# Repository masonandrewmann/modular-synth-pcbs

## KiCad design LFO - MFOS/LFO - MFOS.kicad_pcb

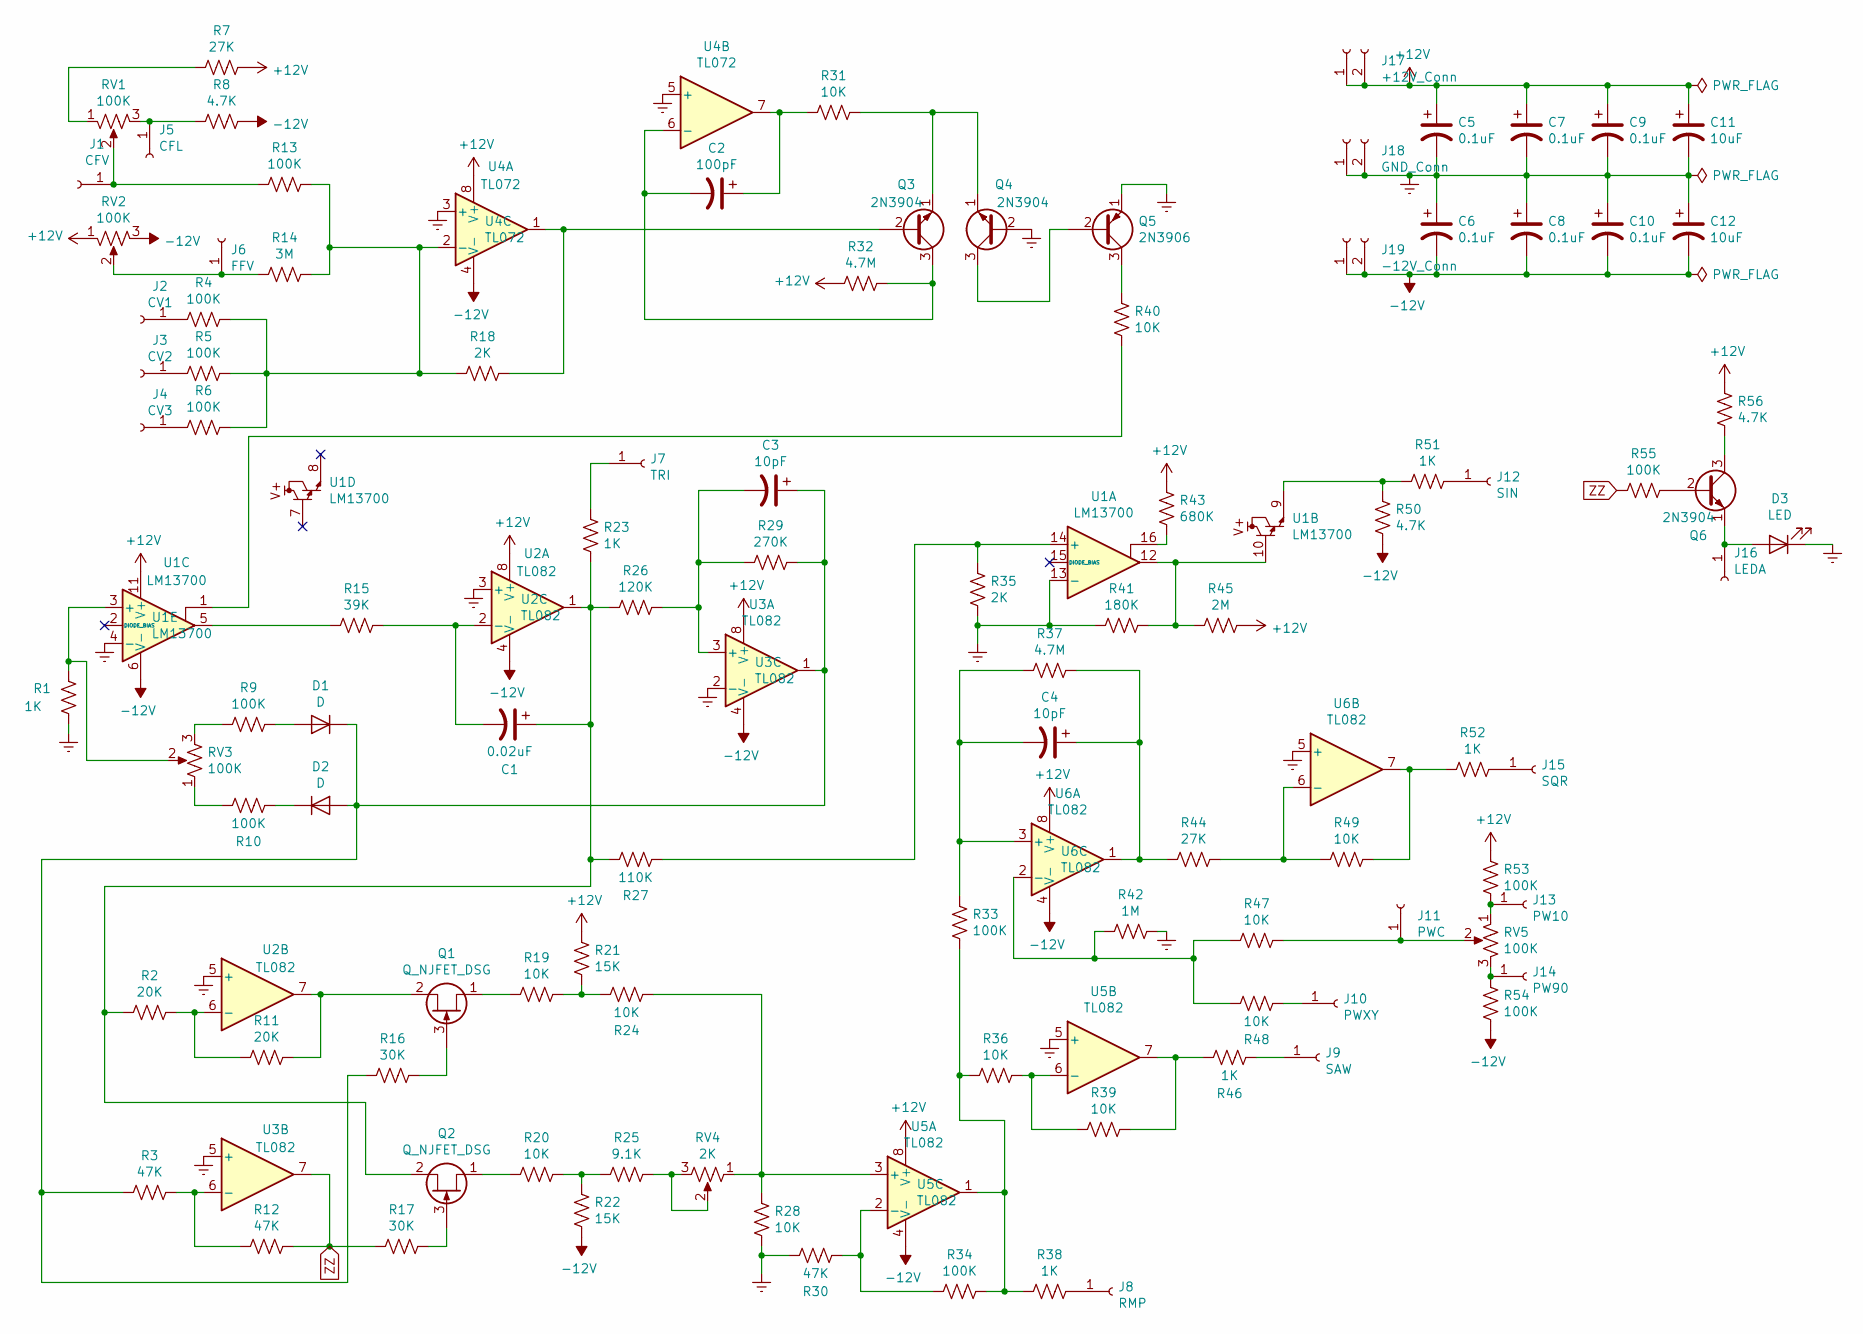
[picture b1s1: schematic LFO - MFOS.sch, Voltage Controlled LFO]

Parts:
C1: 0.02uF; C_Rect_L7.0mm_W2.5mm_P5.00mm
C2: 100pF; C_Rect_L7.0mm_W2.5mm_P5.00mm
C3, C4: 10pF; C_Rect_L7.0mm_W2.5mm_P5.00mm
C5, C6, C7, C8, C9, C10: 0.1uF; C_Rect_L7.0mm_W2.5mm_P5.00mm
C11, C12: 10uF; CP_Radial_D4.0mm_P2.00mm
D1, D2: D; D_T-1_P5.08mm_Horizontal
D3: LED
J1: CFV; SolderWirePad_1x01_Drill1mm
J2: CV1; SolderWirePad_1x01_Drill1mm
J3: CV2; SolderWirePad_1x01_Drill1mm
J4: CV3; SolderWirePad_1x01_Drill1mm
J5: CFL; SolderWirePad_1x01_Drill1mm
J6: FFV; SolderWirePad_1x01_Drill1mm
J7: TRI; SolderWirePad_1x01_Drill1mm
J8: RMP; SolderWirePad_1x01_Drill1mm
J9: SAW; SolderWirePad_1x01_Drill1mm
J10: PWXY; SolderWirePad_1x01_Drill1mm
J11: PWC; SolderWirePad_1x01_Drill1mm
J12: SIN; SolderWirePad_1x01_Drill1mm
J13: PW10; SolderWirePad_1x01_Drill1mm
J14: PW90; SolderWirePad_1x01_Drill1mm
J15: SQR; SolderWirePad_1x01_Drill1mm
J16: LEDA; SolderWirePad_1x01_Drill1mm
J17: +12V_Conn; SolderWirePad_1x02_P3.81mm_Drill1mm
J18: GND_Conn; SolderWirePad_1x02_P3.81mm_Drill1mm
J19: -12V_Conn; SolderWirePad_1x02_P3.81mm_Drill1mm
Q1, Q2: Q_NJFET_DSG; TO-92_Inline_Wide
Q3, Q4, Q6: 2N3904; TO-92_Inline_Wide
Q5: 2N3906; TO-92_Inline_Wide
R1, R23, R38, R46, R51, R52: 1K; R_Axial_DIN0207_L6.3mm_D2.5mm_P7.62mm_Horizontal
R2, R11: 20K; R_Axial_DIN0207_L6.3mm_D2.5mm_P7.62mm_Horizontal
R3, R12, R30: 47K; R_Axial_DIN0207_L6.3mm_D2.5mm_P7.62mm_Horizontal
R4, R5, R6, R9, R10, R13, R33, R34, R53, R54, R55: 100K; R_Axial_DIN0207_L6.3mm_D2.5mm_P7.62mm_Horizontal
R7, R44: 27K; R_Axial_DIN0207_L6.3mm_D2.5mm_P7.62mm_Horizontal
R8, R50, R56: 4.7K; R_Axial_DIN0207_L6.3mm_D2.5mm_P7.62mm_Horizontal
R14: 3M; R_Axial_DIN0207_L6.3mm_D2.5mm_P7.62mm_Horizontal
R15: 39K; R_Axial_DIN0207_L6.3mm_D2.5mm_P7.62mm_Horizontal
R16, R17: 30K; R_Axial_DIN0207_L6.3mm_D2.5mm_P7.62mm_Horizontal
R18, R35: 2K; R_Axial_DIN0207_L6.3mm_D2.5mm_P7.62mm_Horizontal
R19, R20, R24, R28, R31, R36, R39, R40, R47, R48, R49: 10K; R_Axial_DIN0207_L6.3mm_D2.5mm_P7.62mm_Horizontal
R21, R22: 15K; R_Axial_DIN0207_L6.3mm_D2.5mm_P7.62mm_Horizontal
R25: 9.1K; R_Axial_DIN0207_L6.3mm_D2.5mm_P7.62mm_Horizontal
R26: 120K; R_Axial_DIN0207_L6.3mm_D2.5mm_P7.62mm_Horizontal
R27: 110K; R_Axial_DIN0207_L6.3mm_D2.5mm_P7.62mm_Horizontal
R29: 270K; R_Axial_DIN0207_L6.3mm_D2.5mm_P7.62mm_Horizontal
R32, R37: 4.7M; R_Axial_DIN0207_L6.3mm_D2.5mm_P7.62mm_Horizontal
R41: 180K; R_Axial_DIN0207_L6.3mm_D2.5mm_P7.62mm_Horizontal
R42: 1M; R_Axial_DIN0207_L6.3mm_D2.5mm_P7.62mm_Horizontal
R43: 680K; R_Axial_DIN0207_L6.3mm_D2.5mm_P7.62mm_Horizontal
R45: 2M; R_Axial_DIN0207_L6.3mm_D2.5mm_P7.62mm_Horizontal
RV1, RV2, RV5: 100K
RV3: 100K; Potentiometer_Runtron_RM-065_Vertical
RV4: 2K; Potentiometer_Runtron_RM-065_Vertical
U1: LM13700; DIP-16_W7.62mm_Socket
U2, U3, U5, U6: TL082; DIP-8_W7.62mm_Socket
U4: TL072; DIP-8_W7.62mm_Socket

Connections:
+12V: C5.1, C7.1, C9.1, C11.1, J17.1, J17.2, R7.1, R21.2, R32.2, R43.2, R45.1, R53.1, R56.2, RV2.1, U1.11 (V+), U2.8 (V+), U3.8 (V+), U4.8 (V+), U5.8 (V+), U6.8 (V+)
-12V: C6.2, C8.2, C10.2, C12.2, J19.1, J19.2, R8.1, R22.1, R50.1, R54.2, RV2.3, U1.6 (V-), U2.4 (V-), U3.4 (V-), U4.4 (V-), U5.4 (V-), U6.4 (V-)
Earth: C5.2, C6.1, C7.2, C8.1, C9.2, C10.1, C11.2, C12.1, D3.1 (K), J18.1, J18.2, Q4.2 (B), Q5.1 (E), R1.2, R28.1, R30.2, R35.1, R41.2, R42.1, U1.4 (-), U1.13 (-), U2.3 (+), U2.5 (+), U3.2 (-), U3.5 (+), U4.3 (+), U4.5 (+), U5.5 (+), U6.5 (+)
unnamed: C1.1, Q2.2 (S), R2.2, R23.1, R26.2, R27.2, U2.1
unnamed: C1.2, R15.1, U2.2 (-)
unnamed: C2.1, R31.2, U4.7
unnamed: C2.2, Q3.3 (C), R32.1, U4.6 (-)
unnamed: C3.1, D1.1 (K), D2.2 (A), R3.2, R16.2, R29.1, U3.1
unnamed: C3.2, R26.1, R29.2, U3.3 (+)
unnamed: C4.1, R37.1, R44.1, U6.1
unnamed: C4.2, R33.2, R37.2, U6.3 (+)
unnamed: D1.2 (A), R9.1
unnamed: D2.1 (K), R10.1
unnamed: D3.2 (A), J16.1, Q6.1 (E)
unnamed: J1.1, R13.2, RV1.2
unnamed: J2.1, R4.2
unnamed: J3.1, R5.2
unnamed: J4.1, R6.2
unnamed: J5.1, R8.2, RV1.3
unnamed: J6.1, R14.2, RV2.2
unnamed: J7.1, R23.2
unnamed: J8.1, R38.1
unnamed: J9.1, R46.1
unnamed: J10.1, R48.2
unnamed: J11.1, R47.2, RV5.2
unnamed: J12.1, R51.1
unnamed: J13.1, R53.2, RV5.1
unnamed: J14.1, R54.1, RV5.3
unnamed: J15.1, R52.2
unnamed: Q1.1 (D), R19.2
unnamed: Q1.2 (S), R11.1, U2.7
unnamed: Q1.3 (G), R16.1
unnamed: Q2.1 (D), R20.2
unnamed: Q2.3 (G), R17.1
unnamed: Q3.1 (E), Q4.1 (E), R31.1
unnamed: Q3.2 (B), R18.2, U4.1
unnamed: Q4.3 (C), Q5.2 (B)
unnamed: Q5.3 (C), R40.2
unnamed: Q6.2 (B), R55.1
unnamed: Q6.3 (C), R56.1
unnamed: R1.1, RV3.2, U1.3 (+)
unnamed: R7.2, RV1.1
unnamed: R9.2, RV3.3
unnamed: R10.2, RV3.1
unnamed: R2.1, R11.2, U2.6 (-)
unnamed: R3.1, R12.2, U3.6 (-)
unnamed: R4.1, R5.1, R6.1, R13.1, R14.1, R18.1, U4.2 (-)
unnamed: R15.2, U1.5
unnamed: R19.1, R21.1, R24.2
unnamed: R20.1, R22.2, R25.2
unnamed: R24.1, R28.2, RV4.1, U5.3 (+)
unnamed: R25.1, RV4.2, RV4.3
unnamed: R27.1, R35.2, U1.14 (+)
unnamed: R30.1, R34.2, U5.2 (-)
unnamed: R33.1, R34.1, R36.2, R38.2, U5.1
unnamed: R36.1, R39.2, U5.6 (-)
unnamed: R39.1, R46.2, U5.7
unnamed: R40.1, U1.1
unnamed: R41.1, R45.2, U1.10, U1.12
unnamed: R42.2, R47.1, R48.1, U6.2 (-)
unnamed: R43.1, U1.16
unnamed: R44.2, R49.1, U6.6 (-)
unnamed: R49.2, R52.1, U6.7
unnamed: R50.2, R51.2, U1.9
ZZ: R12.1, R17.2, R55.2, U3.7

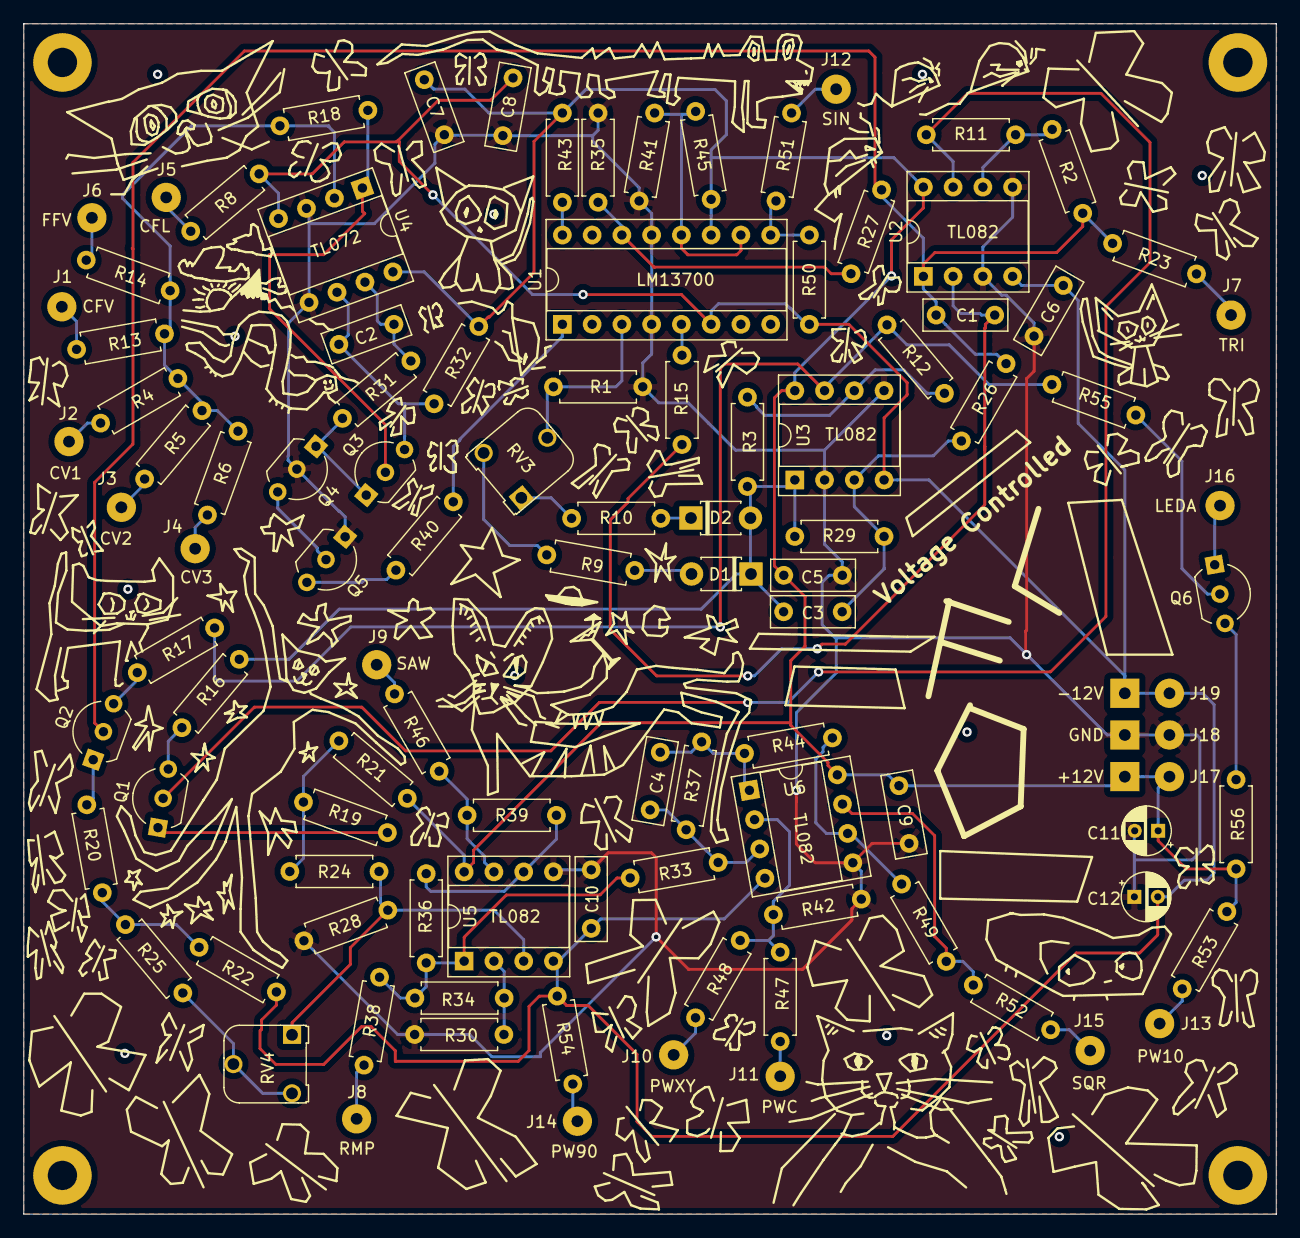
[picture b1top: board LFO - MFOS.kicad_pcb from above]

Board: 2 copper layers, 106.9 x 101.6 mm, 102 parts (0 on the bottom side), 64 nets.

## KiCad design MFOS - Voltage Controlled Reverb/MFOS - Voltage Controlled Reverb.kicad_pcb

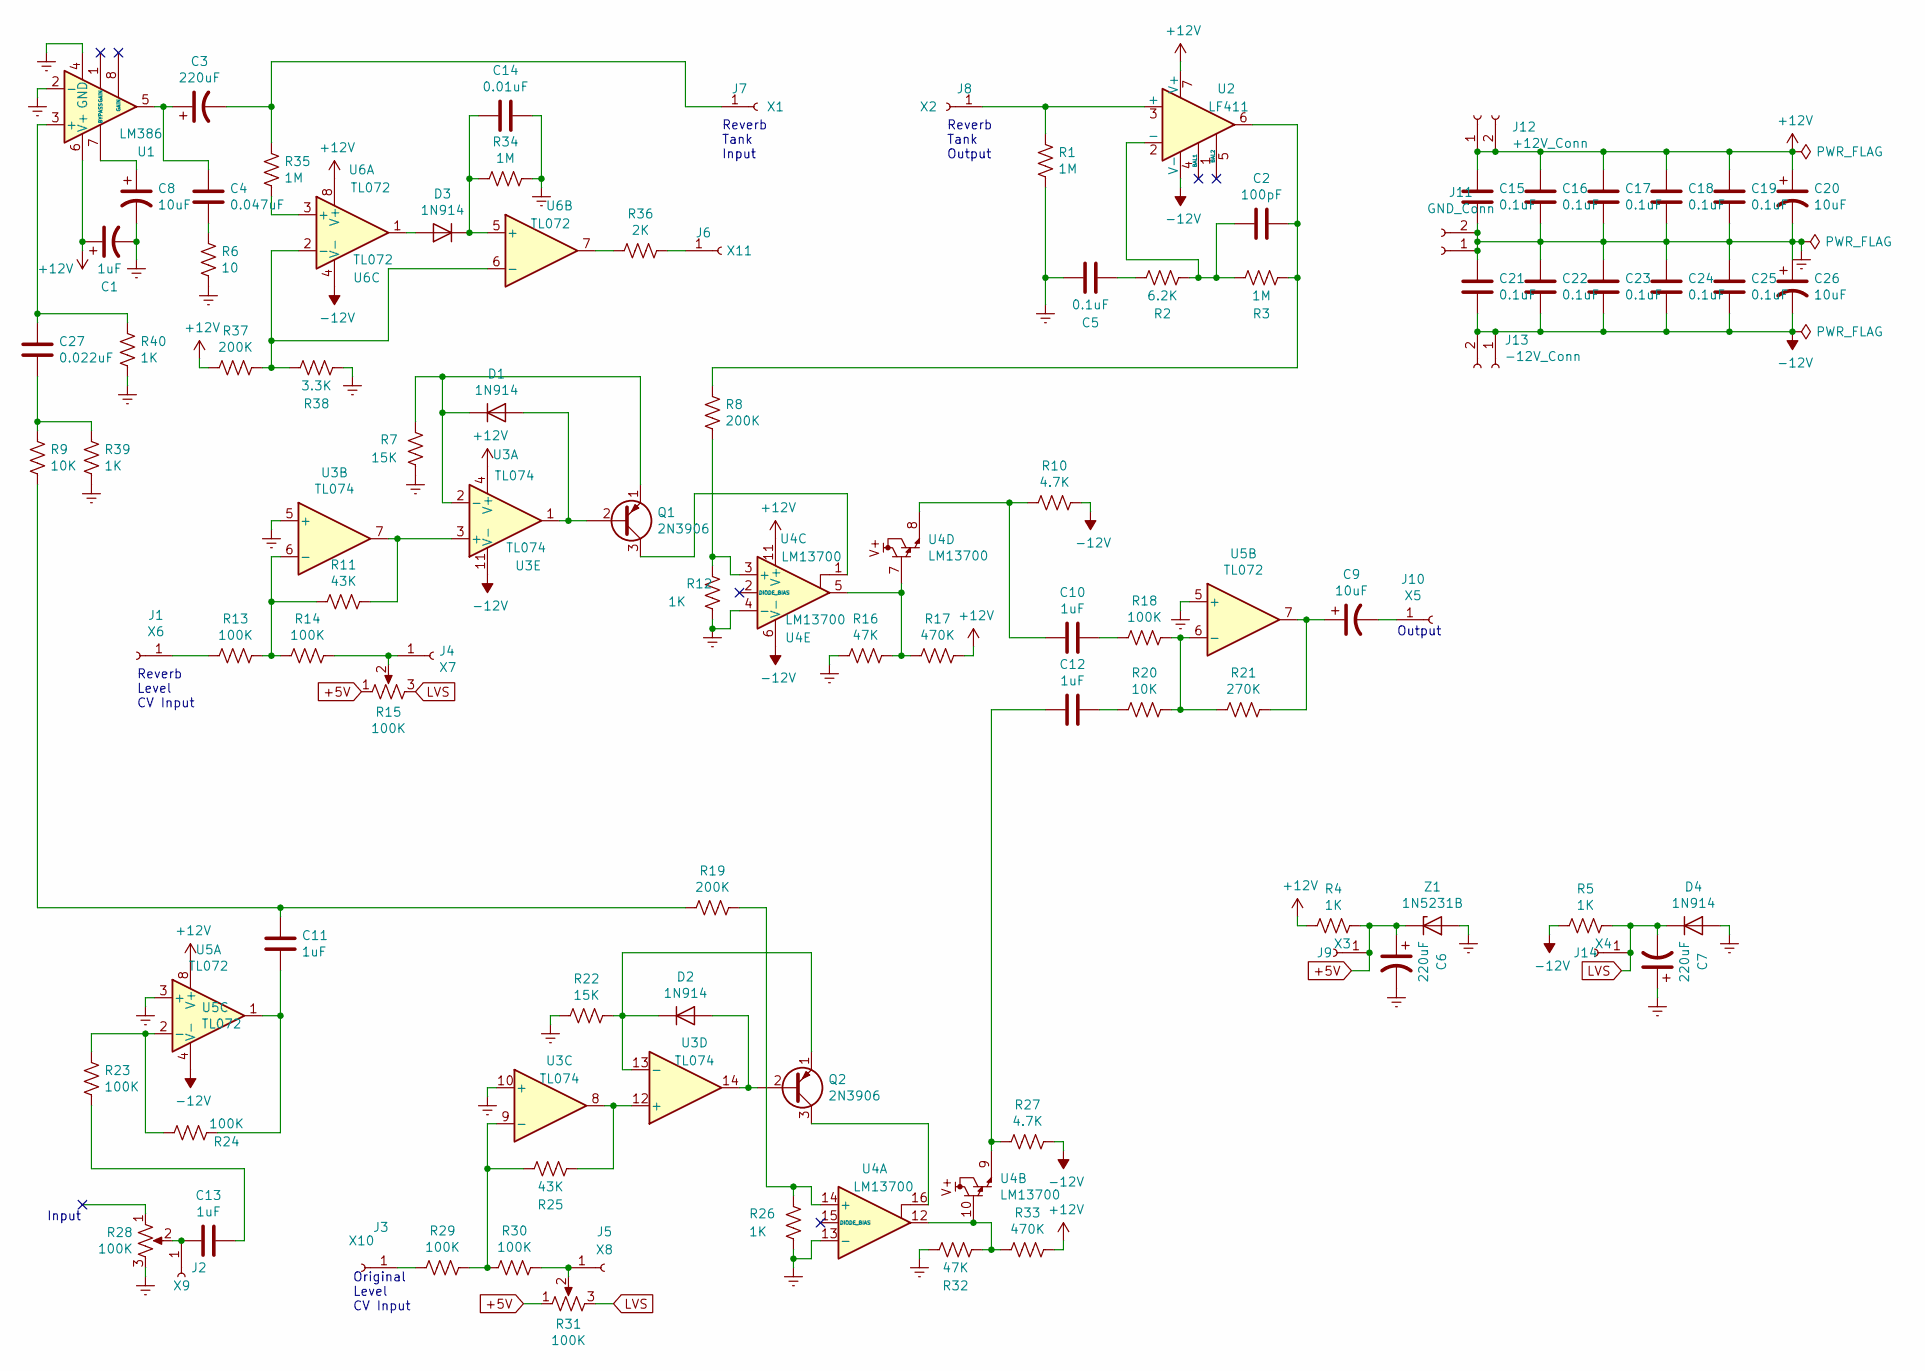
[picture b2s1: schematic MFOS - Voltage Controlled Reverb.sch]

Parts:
C1, C10, C11, C12, C13: 1uF; C_Rect_L7.0mm_W2.5mm_P5.00mm
C2: 100pF; C_Rect_L7.0mm_W2.5mm_P5.00mm
C3: 220uF; C_Rect_L7.0mm_W2.5mm_P5.00mm
C4: 0.047uF; C_Rect_L7.0mm_W2.5mm_P5.00mm
C5, C15, C16, C17, C18, C19, C21, C22, C23, C24, C25: 0.1uF; C_Rect_L7.0mm_W2.5mm_P5.00mm
C6, C7: 220uF; CP_Radial_D8.0mm_P3.50mm
C8, C9, C20, C26: 10uF; CP_Radial_D8.0mm_P3.50mm
C14: 0.01uF; C_Rect_L7.0mm_W2.5mm_P5.00mm
C27: 0.022uF; C_Rect_L7.0mm_W2.5mm_P5.00mm
D1, D2, D3, D4: 1N914; D_T-1_P5.08mm_Horizontal
J1: X6; SolderWirePad_1x01_Drill1mm
J2: X9; SolderWirePad_1x01_Drill1mm
J3: X10; SolderWirePad_1x01_Drill1mm
J4: X7; SolderWirePad_1x01_Drill1mm
J5: X8; SolderWirePad_1x01_Drill1mm
J6: X11; SolderWirePad_1x01_Drill1mm
J7: X1; SolderWirePad_1x01_Drill1mm
J8: X2; SolderWirePad_1x01_Drill1mm
J9: X3; SolderWirePad_1x01_Drill1mm
J10: X5; SolderWirePad_1x01_Drill1mm
J11: GND_Conn; SolderWirePad_1x02_P3.81mm_Drill1mm
J12: +12V_Conn; SolderWirePad_1x02_P3.81mm_Drill1mm
J13: -12V_Conn; SolderWirePad_1x02_P3.81mm_Drill1mm
J14: X4; SolderWirePad_1x01_Drill1mm
Q1, Q2: 2N3906; TO-92_Inline_Wide
R1, R3, R34, R35: 1M; R_Axial_DIN0207_L6.3mm_D2.5mm_P7.62mm_Horizontal
R2: 6.2K; R_Axial_DIN0207_L6.3mm_D2.5mm_P7.62mm_Horizontal
R4, R5, R12, R26, R39, R40: 1K; R_Axial_DIN0207_L6.3mm_D2.5mm_P7.62mm_Horizontal
R6: 10; R_Axial_DIN0207_L6.3mm_D2.5mm_P7.62mm_Horizontal
R7, R22: 15K; R_Axial_DIN0207_L6.3mm_D2.5mm_P7.62mm_Horizontal
R8, R19, R37: 200K; R_Axial_DIN0207_L6.3mm_D2.5mm_P7.62mm_Horizontal
R9, R20: 10K; R_Axial_DIN0207_L6.3mm_D2.5mm_P7.62mm_Horizontal
R10, R27: 4.7K; R_Axial_DIN0207_L6.3mm_D2.5mm_P7.62mm_Horizontal
R11, R25: 43K; R_Axial_DIN0207_L6.3mm_D2.5mm_P7.62mm_Horizontal
R13, R14, R18, R23, R24, R29, R30: 100K; R_Axial_DIN0207_L6.3mm_D2.5mm_P7.62mm_Horizontal
R15, R28, R31: 100K; Valve_Mini_G
R16, R32: 47K; R_Axial_DIN0207_L6.3mm_D2.5mm_P7.62mm_Horizontal
R17, R33: 470K; R_Axial_DIN0207_L6.3mm_D2.5mm_P7.62mm_Horizontal
R21: 270K; R_Axial_DIN0207_L6.3mm_D2.5mm_P7.62mm_Horizontal
R36: 2K; R_Axial_DIN0207_L6.3mm_D2.5mm_P7.62mm_Horizontal
R38: 3.3K; R_Axial_DIN0207_L6.3mm_D2.5mm_P7.62mm_Horizontal
U1: LM386; DIP-8_W7.62mm_Socket
U2: LF411; DIP-8_W7.62mm_Socket
U3: TL074; DIP-14_W7.62mm_Socket
U4: LM13700; DIP-16_W7.62mm_Socket
U5, U6: TL072; DIP-8_W7.62mm_Socket
Z1: 1N5231B; D_T-1_P5.08mm_Horizontal

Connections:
+5V: C6.1, J9.1, R4.2, R15.1, R31.1, Z1.1 (K)
+12V: C1.1, C15.1, C16.1, C17.1, C18.1, C19.1, C20.1, J12.1, J12.2, R4.1, R17.2, R33.2, R37.2, U1.6 (V+), U2.7 (V+), U3.4 (V+), U4.11 (V+), U5.8 (V+), U6.8 (V+)
-12V: C21.2, C22.2, C23.2, C24.2, C25.2, C26.2, J13.1, J13.2, R5.1, R10.2, R27.2, U2.4 (V-), U3.11 (V-), U4.6 (V-), U5.4 (V-), U6.4 (V-)
Earth: C1.2, C5.2, C6.2, C7.1, C8.2, C14.1, C15.2, C16.2, C17.2, C18.2, C19.2, C20.2, C21.1, C22.1, C23.1, C24.1, C25.1, C26.1, D4.2 (A), J11.1, J11.2, R1.1, R6.2, R7.1, R12.1, R16.1, R22.2, R26.1, R28.3, R32.1, R34.1, R38.1, R39.2, R40.2, U1.2 (-), U1.4 (GND), U3.5 (+), U3.10 (+), U4.4 (-), U4.13 (-), U5.3 (+), U5.5 (+), Z1.2 (A)
LVS: C7.2, D4.1 (K), J14.1, R5.2, R15.3, R31.3
unnamed: C2.1, R3.2, R8.1, U2.6
unnamed: C2.2, R2.2, R3.1, U2.2 (-)
unnamed: C3.1, C4.1, U1.5
unnamed: C3.2, J7.1, R35.2
unnamed: C4.2, R6.1
unnamed: C5.1, R2.1
unnamed: C8.1, U1.7 (BYPASS)
unnamed: C9.1, R21.2, U5.7
unnamed: C9.2, J10.1
unnamed: C10.1, R18.1
unnamed: C10.2, R10.1, U4.8
unnamed: C11.1, R24.2, U5.1
unnamed: C11.2, R9.2, R19.2
unnamed: C12.1, R20.1
unnamed: C12.2, R27.1, U4.9
unnamed: C13.1, R23.1
unnamed: C13.2, J2.1, R28.2
unnamed: C14.2, D3.1 (K), R34.2, U6.5 (+)
unnamed: C27.1, R40.1, U1.3 (+)
unnamed: C27.2, R9.1, R39.1
unnamed: D1.1 (K), Q1.1 (E), R7.2, U3.2 (-)
unnamed: D1.2 (A), Q1.2 (B), U3.1
unnamed: D2.1 (K), Q2.1 (E), R22.1, U3.13 (-)
unnamed: D2.2 (A), Q2.2 (B), U3.14
unnamed: D3.2 (A), U6.1
unnamed: J1.1, R13.2
unnamed: J3.1, R29.2
unnamed: J4.1, R14.1, R15.2
unnamed: J5.1, R30.1, R31.2
unnamed: J6.1, R36.1
unnamed: J8.1, R1.2, U2.3 (+)
unnamed: Q1.3 (C), U4.1
unnamed: Q2.3 (C), U4.16
unnamed: R11.1, U3.3 (+), U3.7
unnamed: R11.2, R13.1, R14.2, U3.6 (-)
unnamed: R8.2, R12.2, U4.3 (+)
unnamed: R16.2, R17.1, U4.5, U4.7
unnamed: R18.2, R20.2, R21.1, U5.6 (-)
unnamed: R19.1, R26.2, U4.14 (+)
unnamed: R23.2, R24.1, U5.2 (-)
unnamed: R25.1, U3.8, U3.12 (+)
unnamed: R25.2, R29.1, R30.2, U3.9 (-)
unnamed: R32.2, R33.1, U4.10, U4.12
unnamed: R35.1, U6.3 (+)
unnamed: R36.2, U6.7
unnamed: R37.1, R38.2, U6.2 (-), U6.6 (-)

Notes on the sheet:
Output
Input
Original Level CV Input
Reverb Level CV Input
Reverb Tank Output
Reverb Tank Input

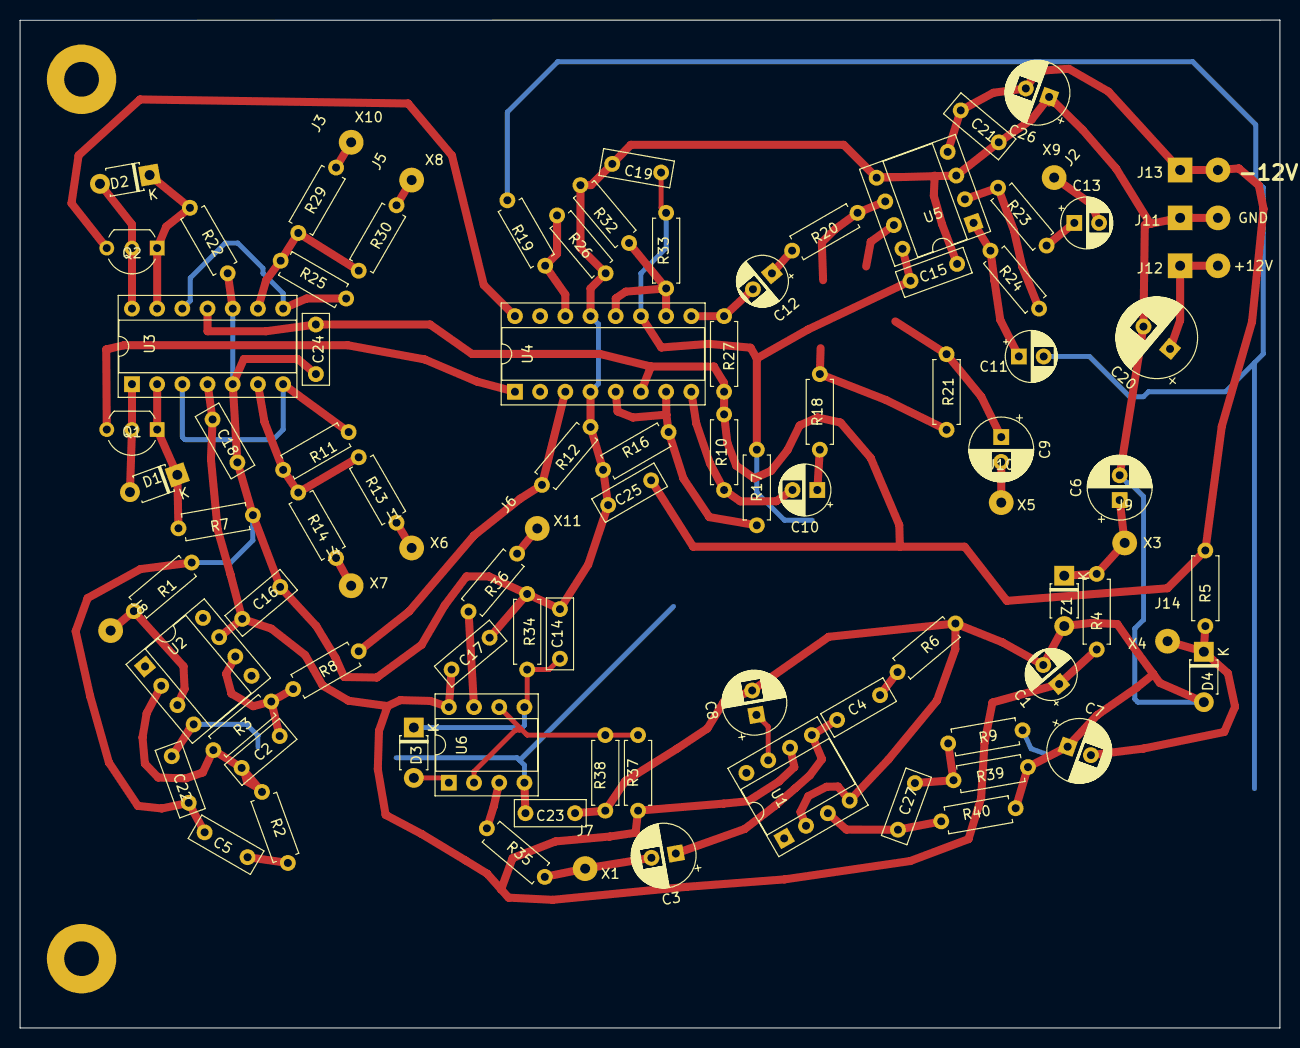
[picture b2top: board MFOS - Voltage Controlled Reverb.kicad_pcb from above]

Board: 2 copper layers, 127.0 x 101.6 mm, 91 parts (0 on the bottom side), 51 nets.

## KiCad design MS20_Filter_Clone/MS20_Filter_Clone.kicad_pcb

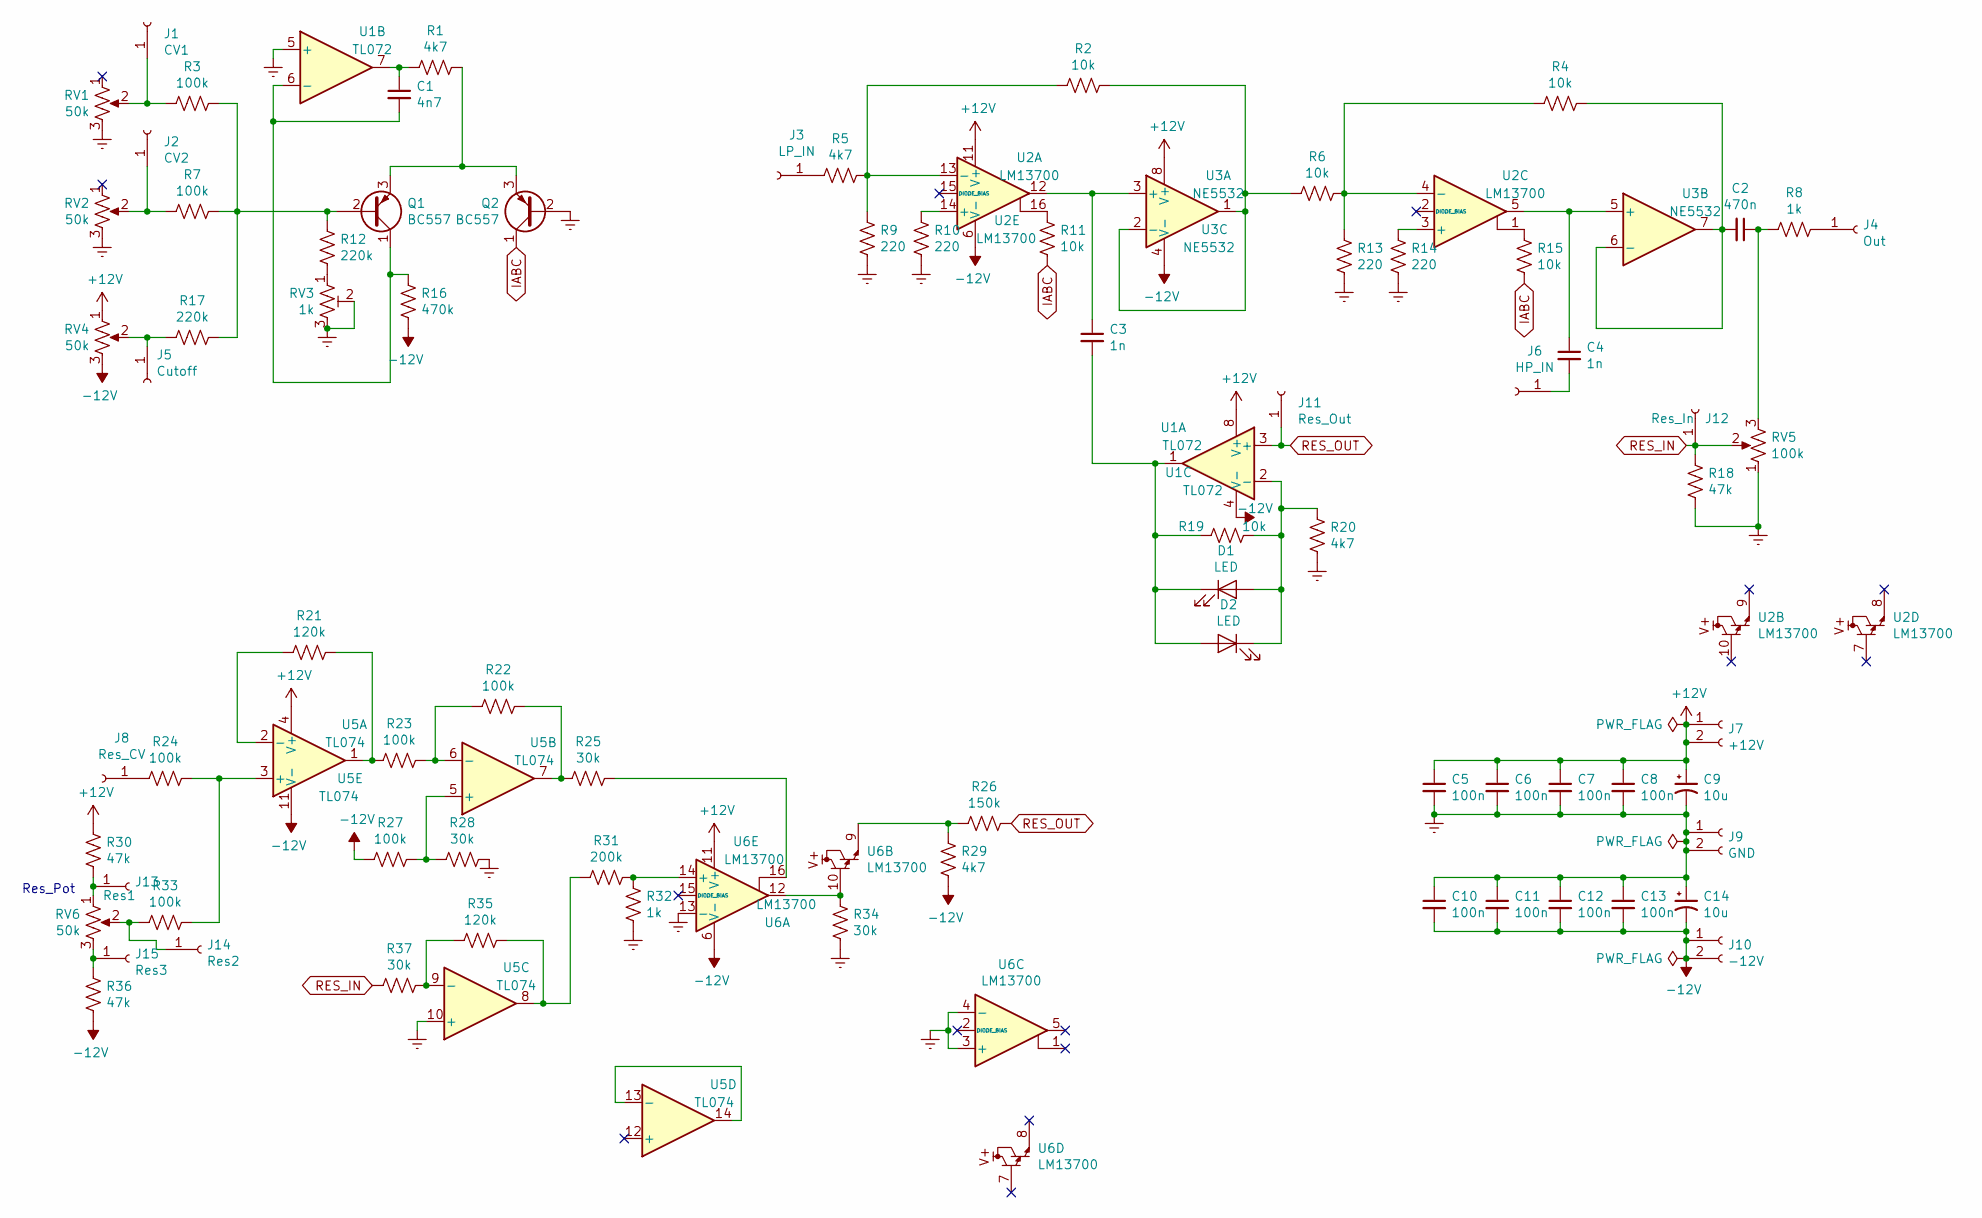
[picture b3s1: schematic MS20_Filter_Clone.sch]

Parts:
C1: 4n7; C_Rect_L7.0mm_W2.5mm_P5.00mm
C2: 470n; C_Rect_L7.0mm_W2.5mm_P5.00mm
C3, C4: 1n; C_Rect_L7.0mm_W2.5mm_P5.00mm
C5, C6, C7, C8, C10, C11, C12, C13: 100n; C_Rect_L7.0mm_W2.5mm_P5.00mm
C9, C14: 10u; CP_Radial_D5.0mm_P2.0mm_Bigger_Holes
D1, D2: LED; LED_D3.0mm
J1: CV1; SolderWirePad_1x01_Drill1mm
J2: CV2; SolderWirePad_1x01_Drill1mm
J3: LP_IN; SolderWirePad_1x01_Drill1mm
J4: Out; SolderWirePad_1x01_Drill1mm
J5: Cutoff; SolderWirePad_1x01_Drill1mm
J6: HP_IN; SolderWirePad_1x01_Drill1mm
J7: +12V; SolderWirePad_1x02_P3.81mm_Drill1mm
J8: Res_CV; SolderWirePad_1x01_Drill1mm
J9: GND; SolderWirePad_1x02_P3.81mm_Drill1mm
J10: -12V; SolderWirePad_1x02_P3.81mm_Drill1mm
J11: Res_Out; SolderWirePad_1x01_Drill1mm
J12: Res_In; SolderWirePad_1x01_Drill1mm
J13: Res1; SolderWirePad_1x01_Drill1mm
J14: Res2; SolderWirePad_1x01_Drill1mm
J15: Res3; SolderWirePad_1x01_Drill1mm
Q1, Q2: BC557; TO-92_Inline_Wide
R1, R5, R20, R29: 4k7; R_Axial_DIN0207_L6.3mm_D2.5mm_P7.62mm_Horizontal
R2, R4, R6, R11, R15, R19: 10k; R_Axial_DIN0207_L6.3mm_D2.5mm_P7.62mm_Horizontal
R3, R7, R22, R23, R24, R27, R33: 100k; R_Axial_DIN0207_L6.3mm_D2.5mm_P7.62mm_Horizontal
R8, R32: 1k; R_Axial_DIN0207_L6.3mm_D2.5mm_P7.62mm_Horizontal
R9, R10, R13, R14: 220; R_Axial_DIN0207_L6.3mm_D2.5mm_P7.62mm_Horizontal
R12, R17: 220k; R_Axial_DIN0207_L6.3mm_D2.5mm_P7.62mm_Horizontal
R16: 470k; R_Axial_DIN0207_L6.3mm_D2.5mm_P7.62mm_Horizontal
R18, R30, R36: 47k; R_Axial_DIN0207_L6.3mm_D2.5mm_P7.62mm_Horizontal
R21, R35: 120k; R_Axial_DIN0207_L6.3mm_D2.5mm_P7.62mm_Horizontal
R25, R28, R34, R37: 30k; R_Axial_DIN0207_L6.3mm_D2.5mm_P7.62mm_Horizontal
R26: 150k; R_Axial_DIN0207_L6.3mm_D2.5mm_P7.62mm_Horizontal
R31: 200k; R_Axial_DIN0207_L6.3mm_D2.5mm_P7.62mm_Horizontal
RV1, RV2, RV4, RV6: 50k
RV3: 1k; Potentiometer_Runtron_RM-065_Vertical
RV5: 100k; Potentiometer_Runtron_RM-065_Vertical
U1: TL072; DIP-8_W7.62mm_Socket
U2, U6: LM13700; DIP-16_W7.62mm_Socket
U3: NE5532; DIP-8_W7.62mm_Socket
U5: TL074; DIP-14_W7.62mm_Socket

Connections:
+12V: C5.1, C6.1, C7.1, C8.1, C9.1, J7.1, J7.2, R30.2, RV4.1, U1.8 (V+), U2.11 (V+), U3.8 (V+), U5.4 (V+), U6.11 (V+)
-12V: C10.2, C11.2, C12.2, C13.2, C14.2, J10.1, J10.2, R16.1, R27.1, R29.2, R36.1, RV4.3, U1.4 (V-), U2.6 (V-), U3.4 (V-), U5.11 (V-), U6.6 (V-)
Earth: C5.2, C6.2, C7.2, C8.2, C9.2, C10.1, C11.1, C12.1, C13.1, C14.1, J9.1, J9.2, Q2.2 (B), R9.1, R10.1, R13.1, R14.1, R18.1, R20.2, R28.2, R32.2, R34.2, RV1.3, RV2.3, RV3.2, RV3.3, RV5.1, U1.5 (+), U5.10 (+), U6.3 (+), U6.4 (-), U6.13 (-)
IABC: Q2.1 (C), R11.1, R15.1
unnamed: C1.1, R1.2, U1.7
unnamed: C1.2, Q1.1 (C), R16.2, U1.6 (-)
unnamed: C2.1, R8.1, RV5.3
unnamed: C2.2, R4.2, U3.6 (-), U3.7
unnamed: C3.1, U2.12, U3.3 (+)
unnamed: C3.2, D1.1 (K), D2.2 (A), R19.1, U1.1
unnamed: C4.1, U2.5, U3.5 (+)
unnamed: C4.2, J6.1
unnamed: D1.2 (A), D2.1 (K), R19.2, R20.1, U1.2 (-)
unnamed: J1.1, R3.2, RV1.2
unnamed: J2.1, R7.2, RV2.2
unnamed: J3.1, R5.1
unnamed: J4.1, R8.2
unnamed: J5.1, R17.2, RV4.2
unnamed: J8.1, R24.2
unnamed: J13.1, R30.1, RV6.1
unnamed: J14.1, R33.2, RV6.2
unnamed: J15.1, R36.2, RV6.3
unnamed: Q1.2 (B), R3.1, R7.1, R12.2, R17.1
unnamed: Q1.3 (E), Q2.3 (E), R1.1
unnamed: R2.1, R5.2, R9.2, U2.13 (-)
unnamed: R2.2, R6.1, U3.1, U3.2 (-)
unnamed: R10.2, U2.14 (+)
unnamed: R11.2, U2.16
unnamed: R12.1, RV3.1
unnamed: R4.1, R6.2, R13.2, U2.4 (-)
unnamed: R14.2, U2.3 (+)
unnamed: R15.2, U2.1
unnamed: R21.1, R23.2, U5.1
unnamed: R21.2, U5.2 (-)
unnamed: R22.1, R25.1, U5.7
unnamed: R22.2, R23.1, U5.6 (-)
unnamed: R24.1, R33.1, U5.3 (+)
unnamed: R25.2, U6.16
unnamed: R26.2, R29.1, U6.9
unnamed: R27.2, R28.1, U5.5 (+)
unnamed: R31.1, R35.1, U5.8
unnamed: R31.2, R32.1, U6.14 (+)
unnamed: R34.1, U6.10, U6.12
unnamed: R35.2, R37.1, U5.9 (-)
unnamed: U5.13 (-), U5.14
RES_IN: J12.1, R18.2, R37.2, RV5.2
RES_OUT: J11.1, R26.1, U1.3 (+)

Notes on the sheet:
Res_Pot

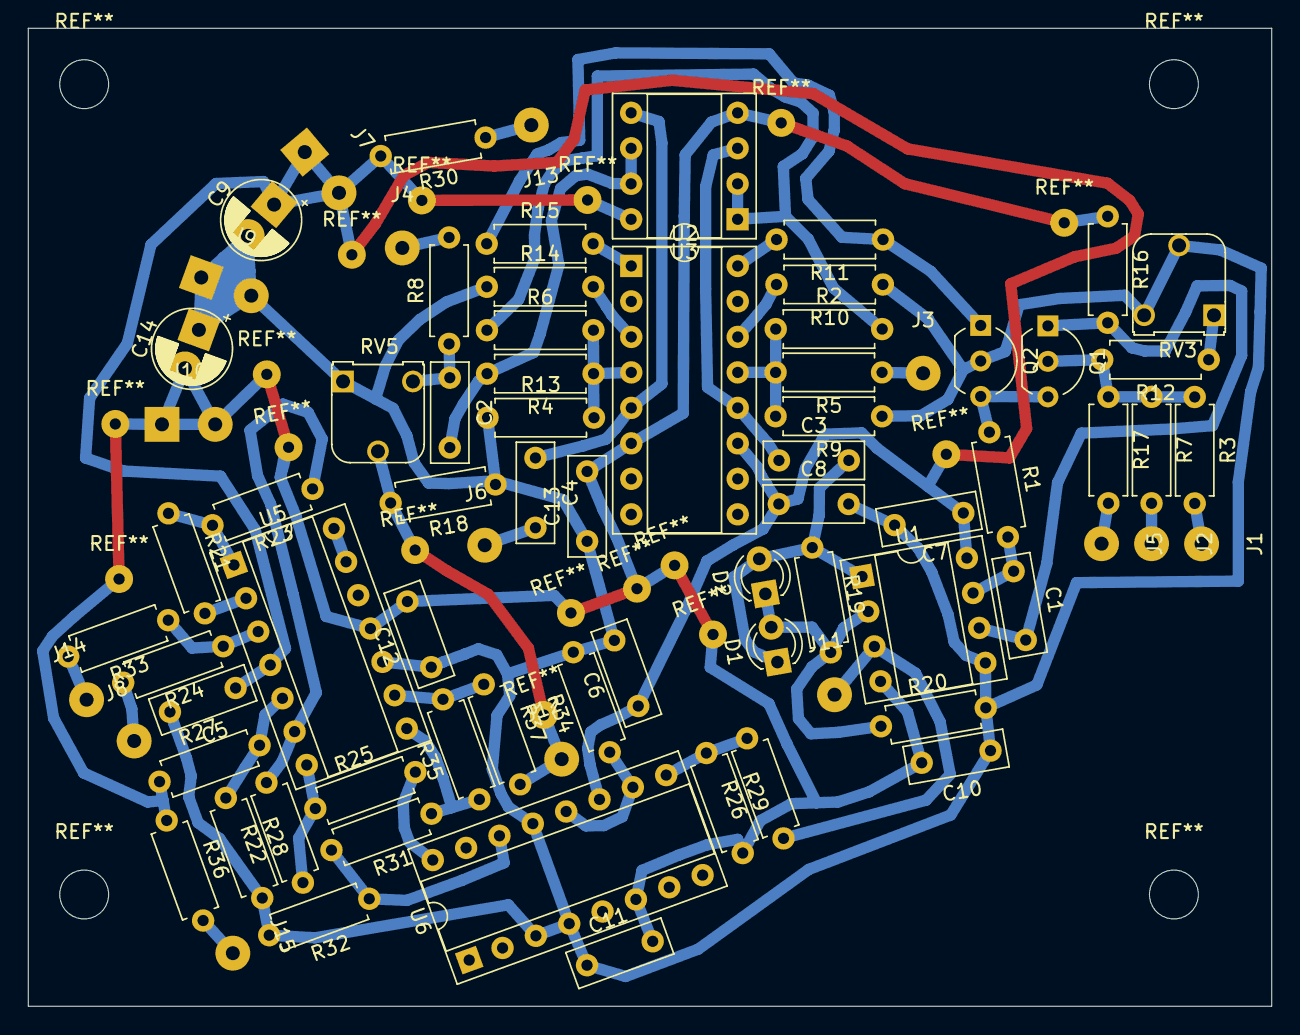
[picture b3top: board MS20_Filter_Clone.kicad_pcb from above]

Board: 2 copper layers, 89.0 x 70.0 mm, 77 parts (0 on the bottom side), 47 nets.
